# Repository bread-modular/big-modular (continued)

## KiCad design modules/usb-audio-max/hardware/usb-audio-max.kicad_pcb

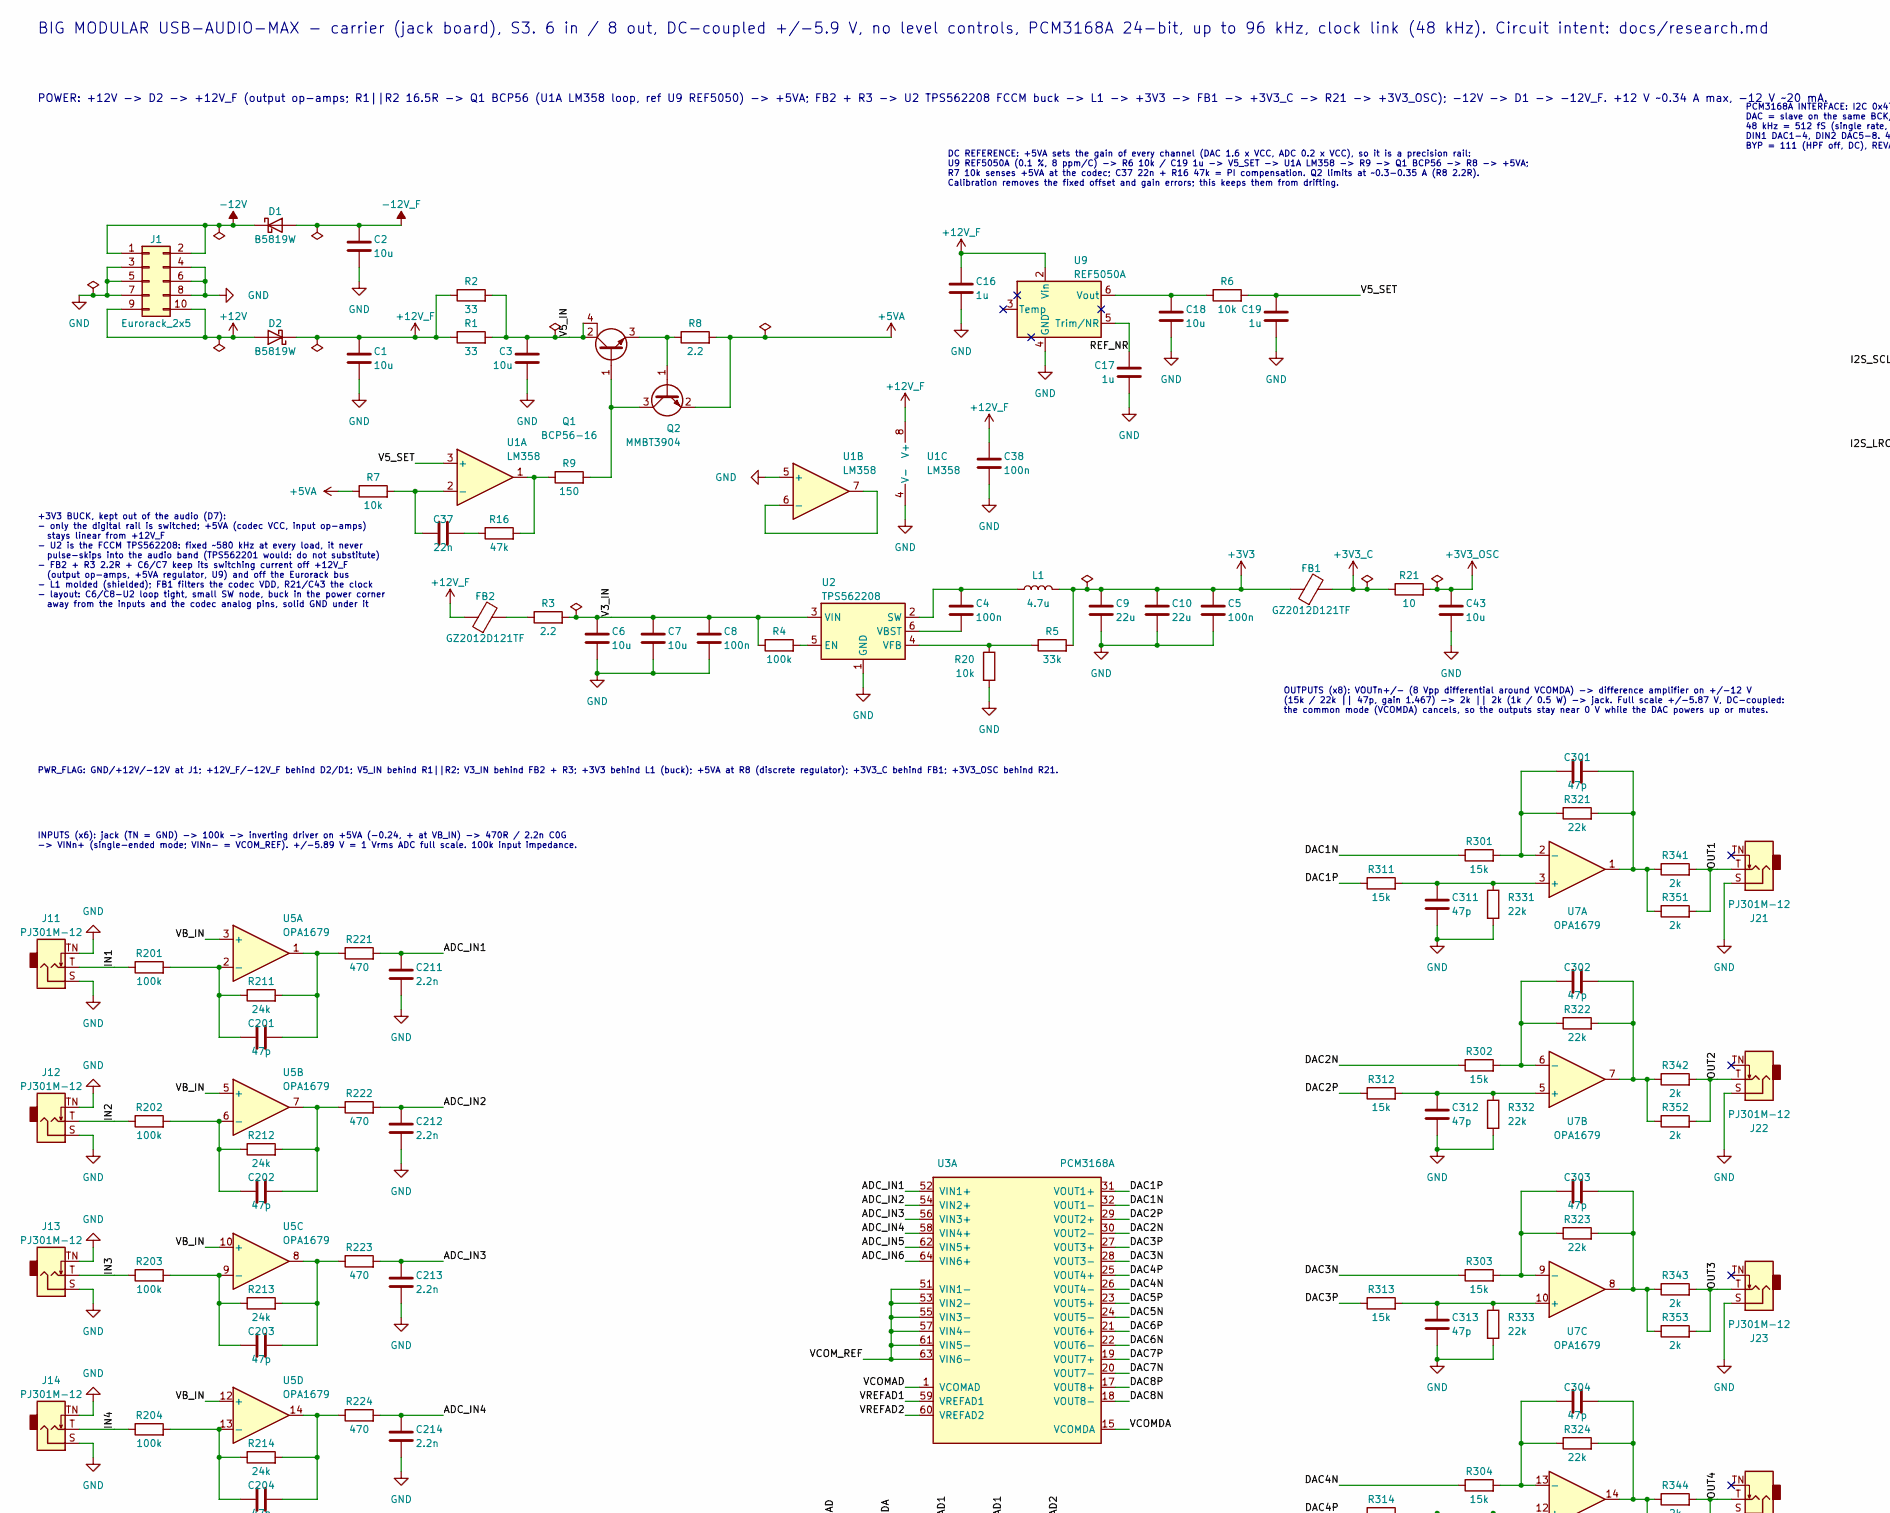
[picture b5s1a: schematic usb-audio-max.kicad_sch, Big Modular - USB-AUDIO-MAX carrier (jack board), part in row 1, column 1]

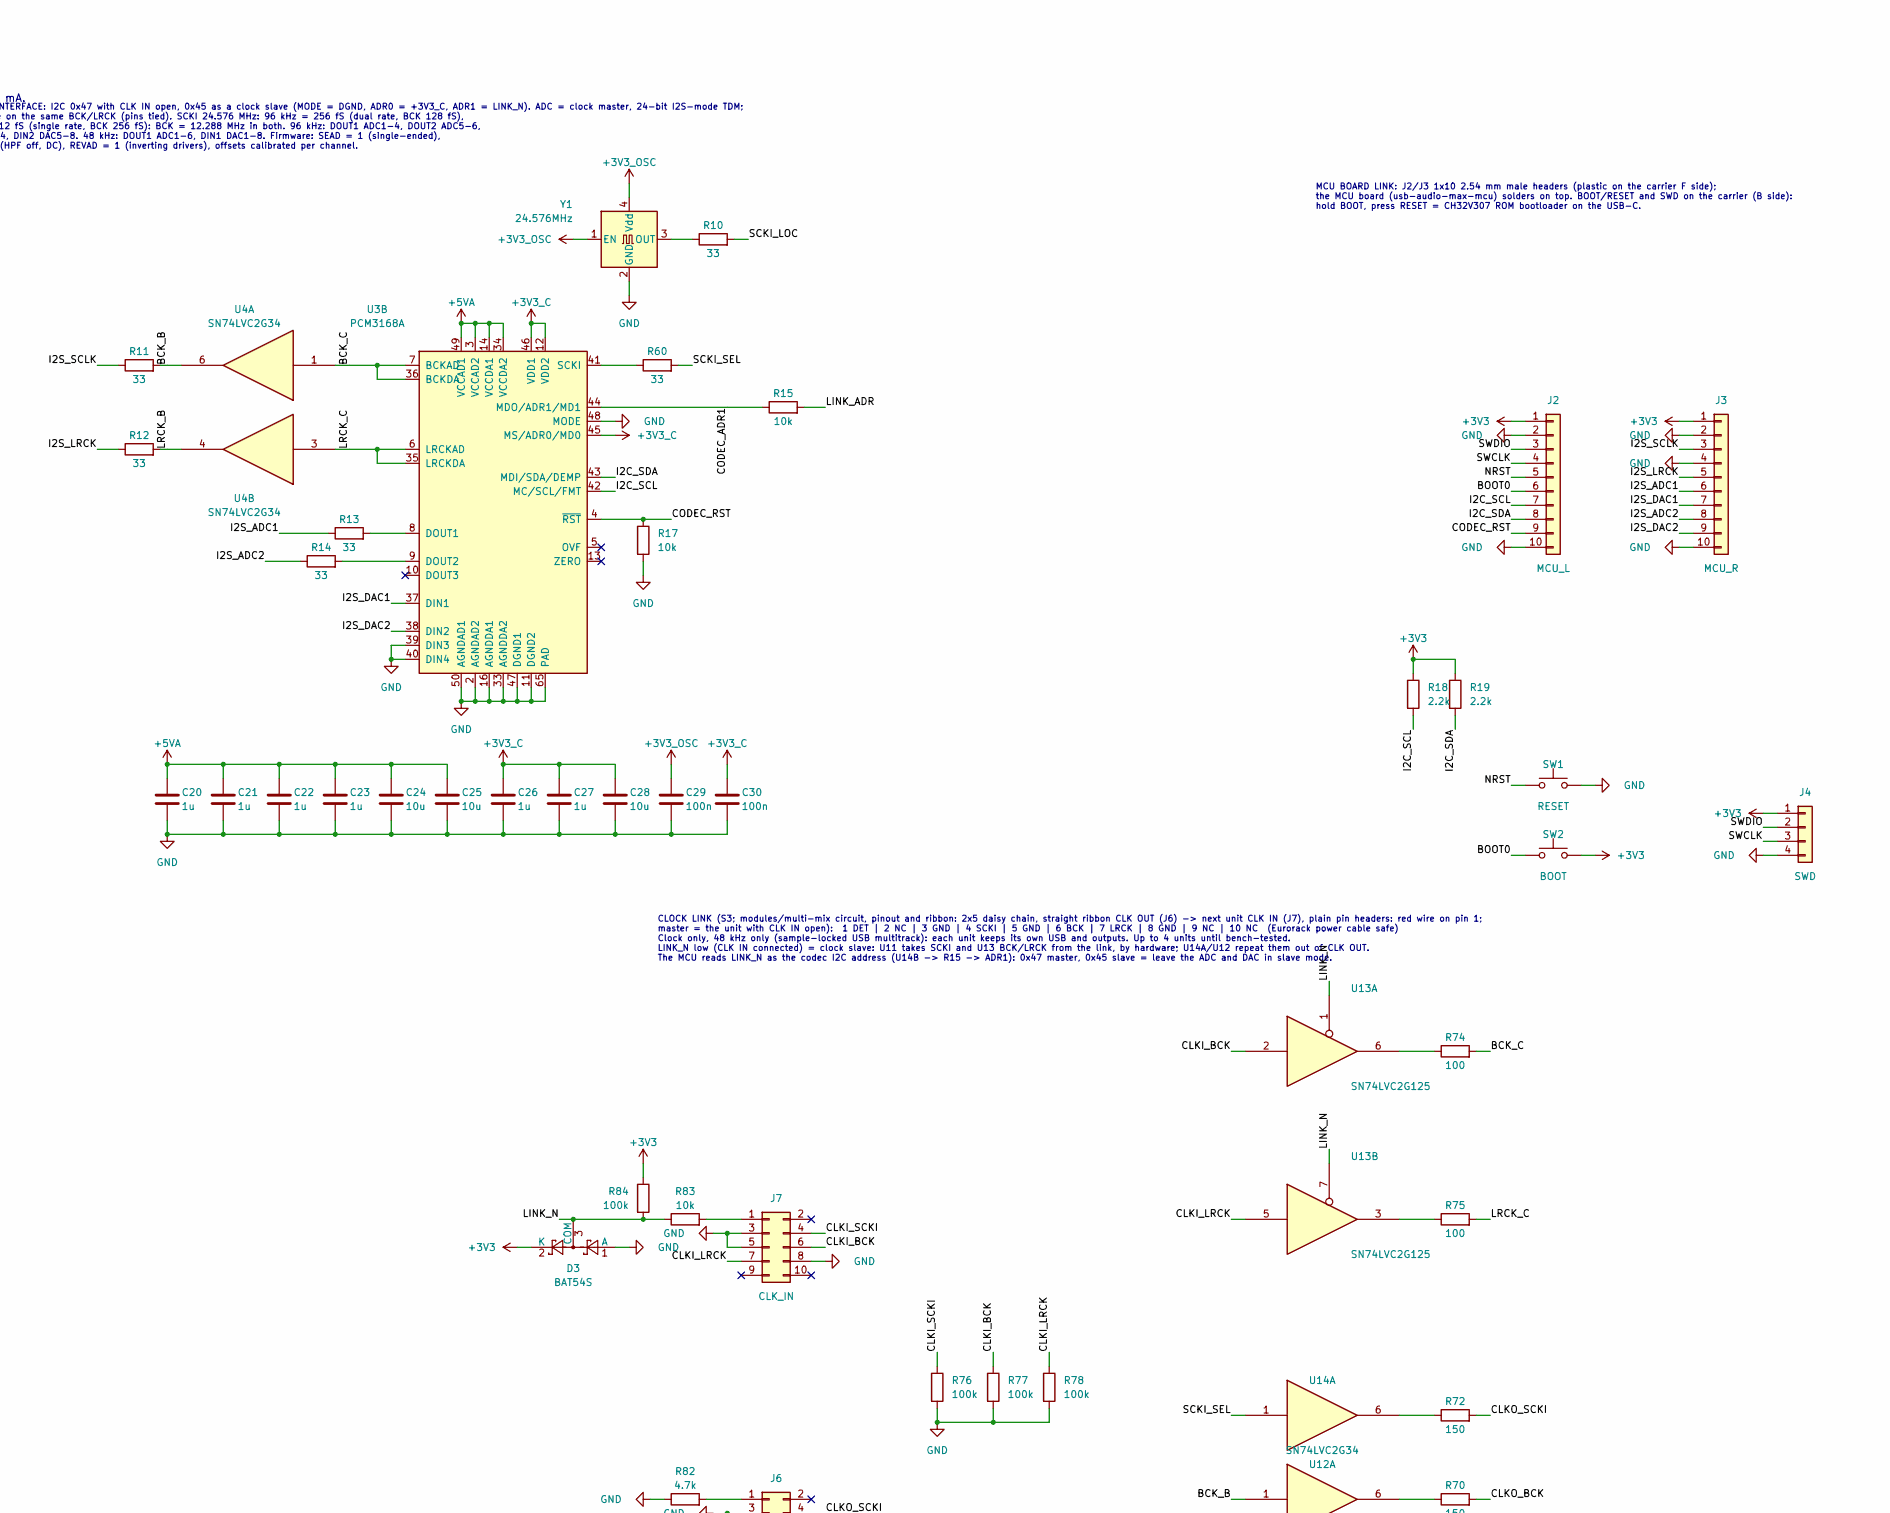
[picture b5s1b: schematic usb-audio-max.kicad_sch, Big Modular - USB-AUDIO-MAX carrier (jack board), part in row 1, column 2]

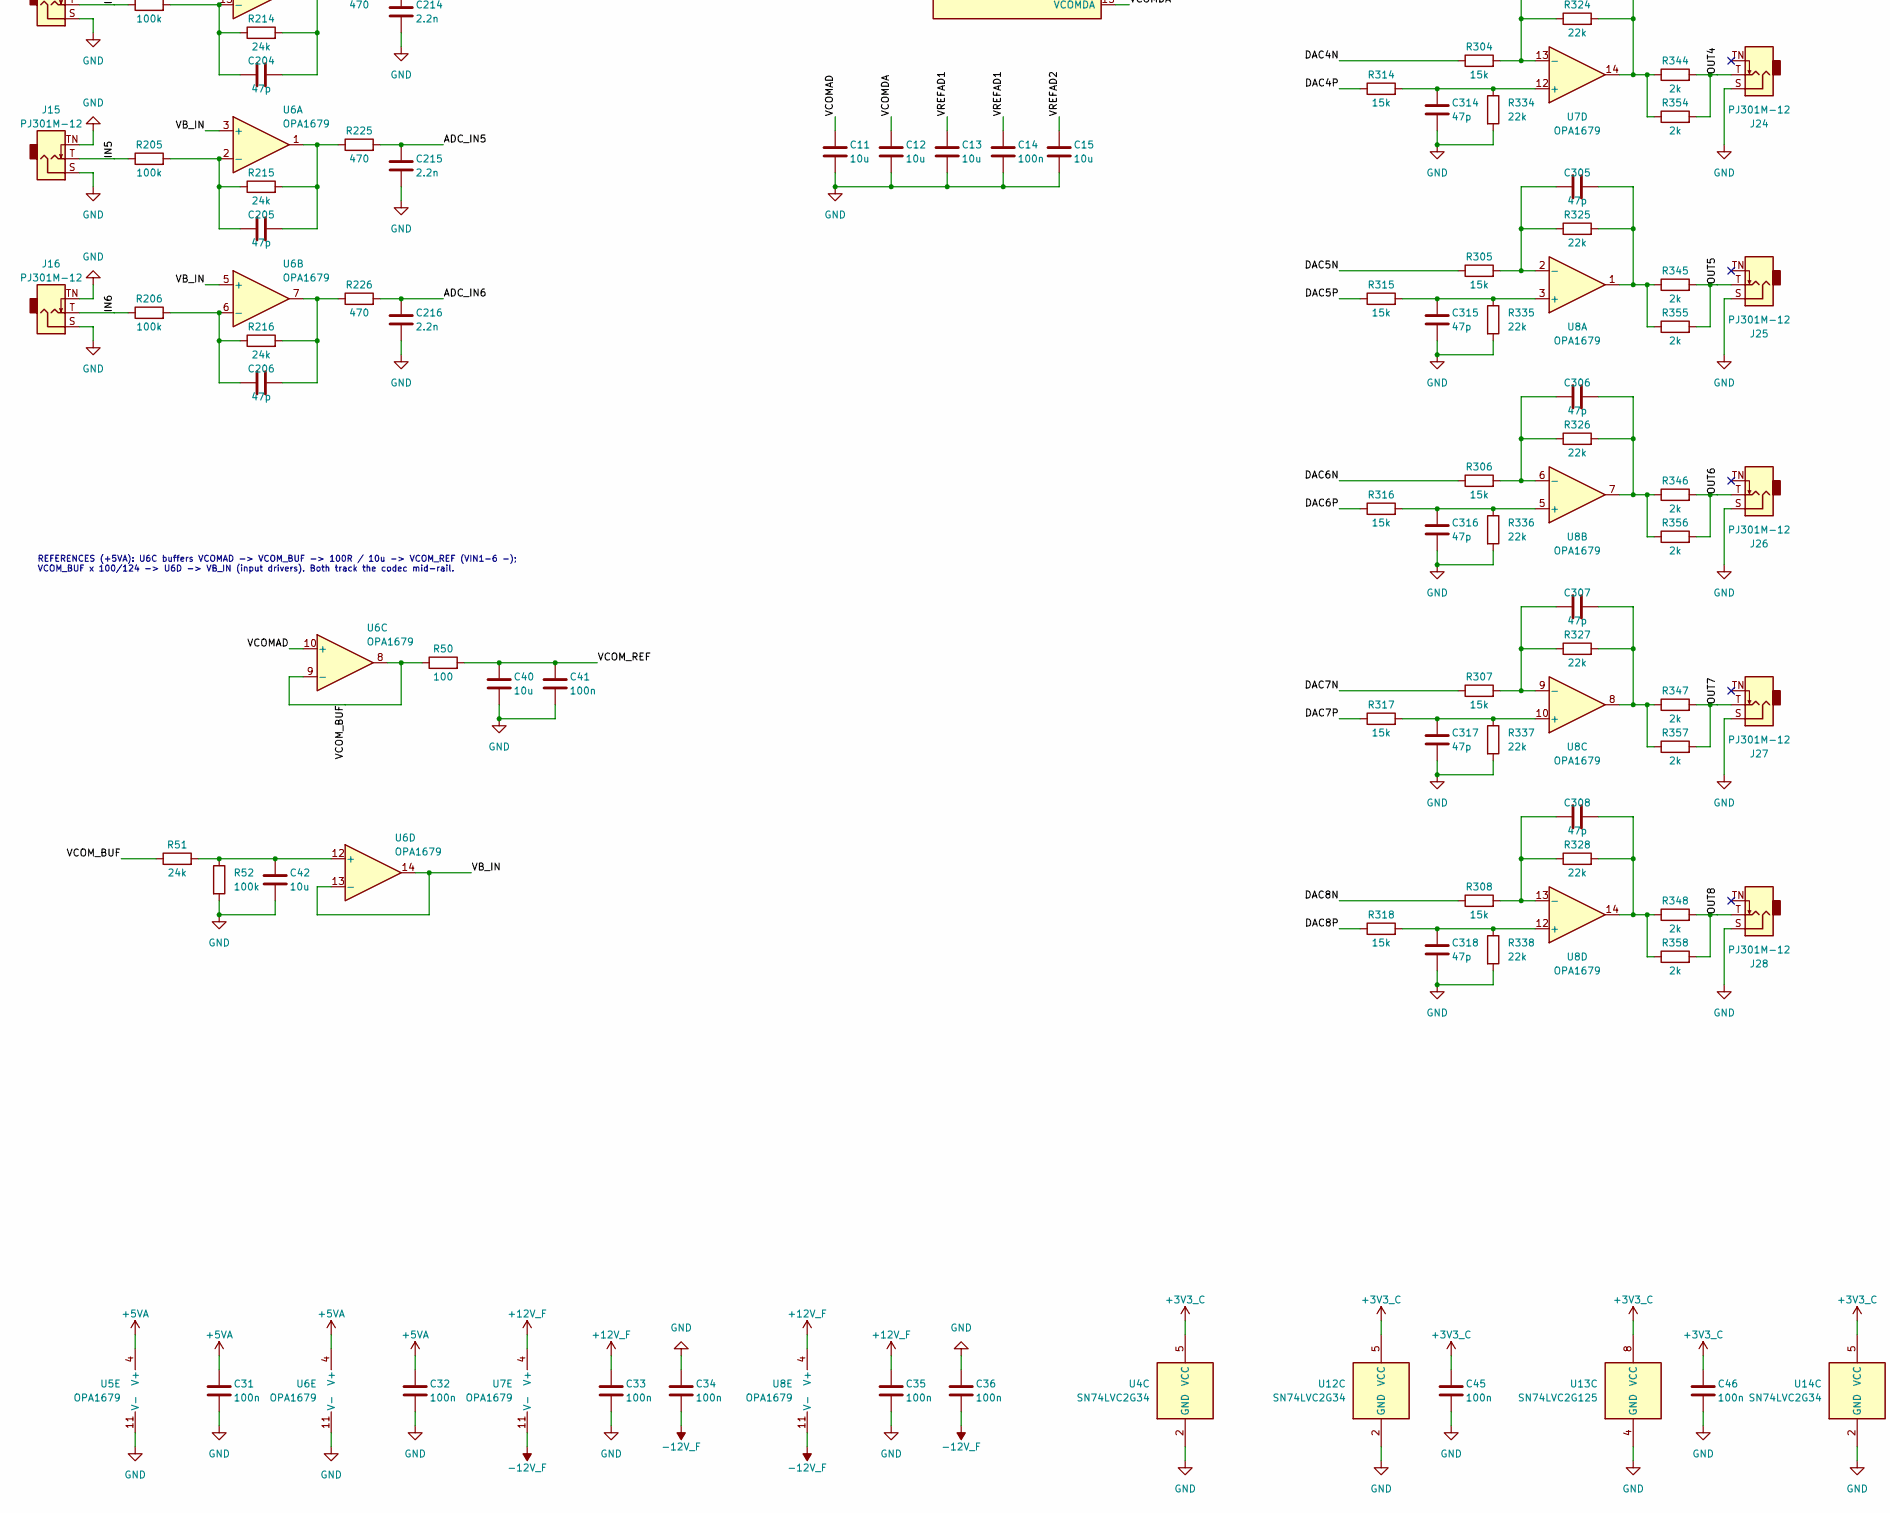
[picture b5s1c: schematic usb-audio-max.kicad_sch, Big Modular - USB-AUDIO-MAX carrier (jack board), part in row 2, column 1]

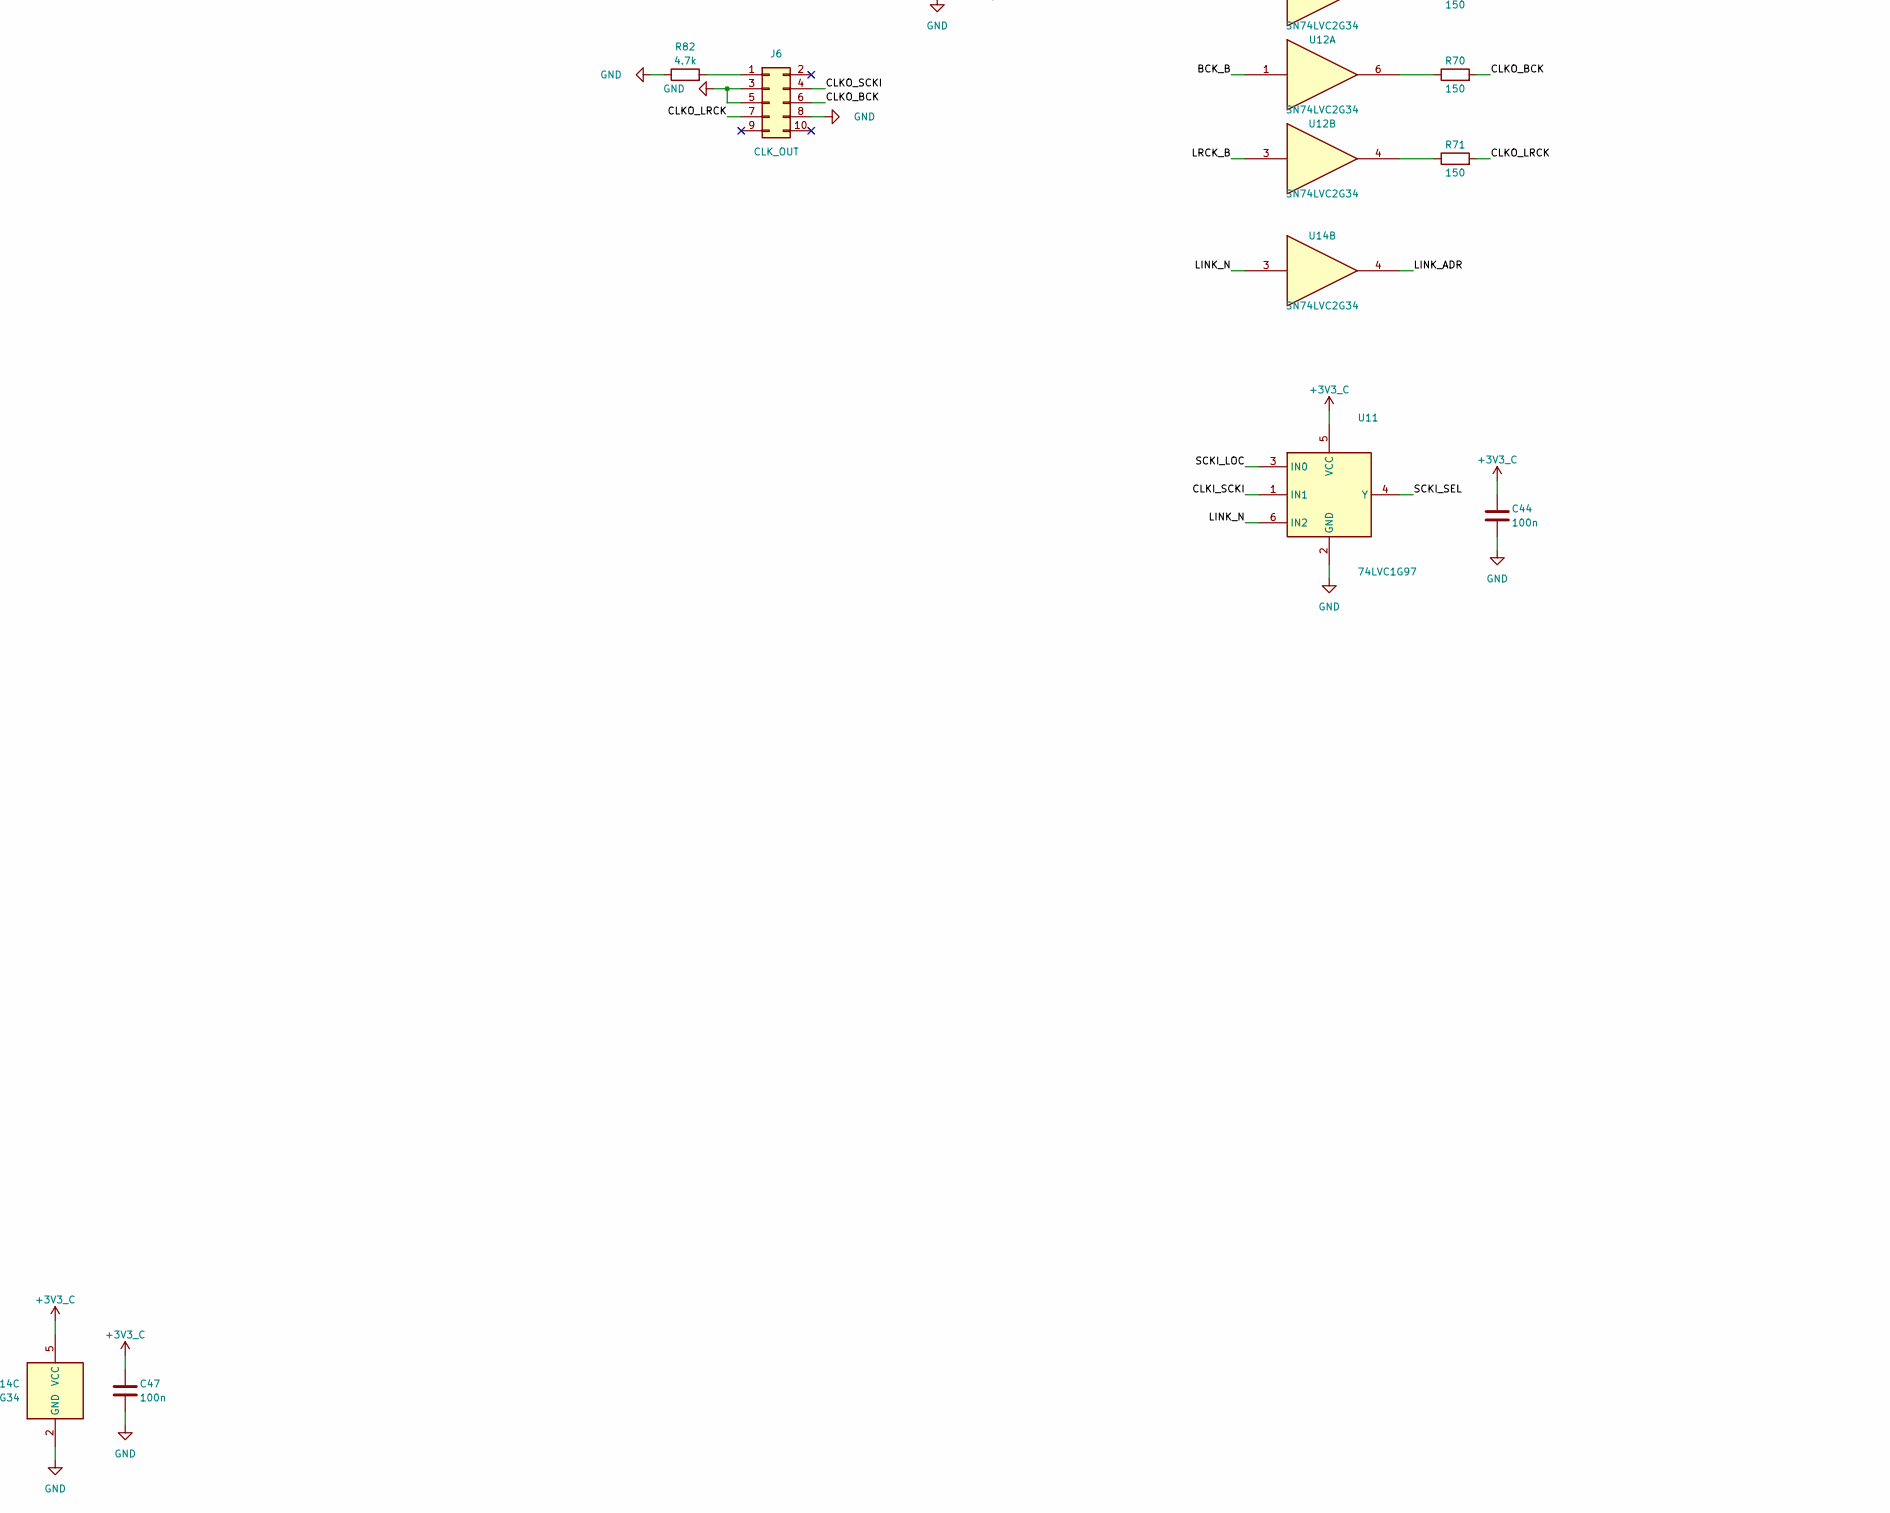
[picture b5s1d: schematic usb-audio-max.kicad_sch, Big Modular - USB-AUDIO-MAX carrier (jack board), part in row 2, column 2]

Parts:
C1, C2, C3, C11, C12, C13, C15, C18, C24, C25, C28, C40, C42, C43: 10u; C_0805_2012Metric; Voltage 25V; MPN CL21A106KAYNNNE; LCSC C15850
C4, C5, C8, C14, C29, C30, C31, C32, C33, C34, C35, C36, C38, C41, C44, C45, C46, C47: 100n; C_0603_1608Metric; Voltage 50V; MPN CC0603KRX7R9BB104; LCSC C14663
C6, C7: 10u; C_1206_3216Metric; Voltage 50V; MPN CL31A106KBHNNNE; LCSC C13585
C9, C10: 22u; C_0805_2012Metric; Voltage 25V; MPN CL21A226MAQNNNE; LCSC C45783
C16, C17, C19, C20, C21, C22, C23, C26, C27: 1u; C_0603_1608Metric; Voltage 50V; MPN CL10A105KB8NNNC; LCSC C15849
C37: 22n; C_0603_1608Metric; Voltage 50V; MPN CL10B223KB8NNNC; LCSC C21122
C201, C202, C203, C204, C205, C206, C301, C302, C303, C304, C305, C306, C307, C308, C311, C312, C313, C314, C315, C316, C317, C318: 47p; C_0603_1608Metric; Voltage 50V; MPN CL10C470JB8NNNC; LCSC C1671
C211, C212, C213, C214, C215, C216: 2.2n; C_0603_1608Metric; Voltage 50V; MPN CC0603JRNPO9BN222; LCSC C107043
D1, D2: B5819W; D_SOD-123; MPN B5819W SL; LCSC C8598
D3: BAT54S; SOT-23; MPN BAT54S,215; LCSC C47546
FB1, FB2: GZ2012D121TF; C_0805_2012Metric; MPN GZ2012D121TF; LCSC C5671
J1: Eurorack_2x5; PinHeader_2x05_P2.54mm_Vertical
J2: MCU_L; PinHeader_1x10_P2.54mm_Vertical; MPN 2.54 mm 1x10 male pin header (2.5 mm pl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
J3: MCU_R; PinHeader_1x10_P2.54mm_Vertical; MPN 2.54 mm 1x10 male pin header (2.5 mm pl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
J4: SWD; PinHeader_1x04_P2.54mm_Vertical
J6: CLK_OUT; PinHeader_2x05_P2.54mm_Vertical
J7: CLK_IN; PinHeader_2x05_P2.54mm_Vertical
J11, J12, J13, J14, J15, J16, J21, J22, J23, J24, J25, J26, J27, J28: PJ301M-12; Jack_3.5mm_QingPu_WQP-PJ301M-12_Vertical
L1: 4.7u; L_Sunlord_MWSA0402S; MPN MWSA0402S-4R7MT; LCSC C408337
Q1: BCP56-16; SOT-223; MPN BCP56-16,115; LCSC C92221
Q2: MMBT3904; SOT-23; MPN MMBT3904; LCSC C20526
R1, R2: 33; R_2512_6332Metric; MPN 25121WF330JT4E; LCSC C53728
R3, R8: 2.2; R_1206_3216Metric; Tolerance 1%; MPN AC1206FR-072R2L; LCSC C144499
R4, R52, R76, R77, R78, R84, R201, R202, R203, R204, R205, R206: 100k; R_0603_1608Metric; MPN 0603WAF1003T5E; LCSC C25803
R5: 33k; R_0603_1608Metric; MPN 0603WAF3302T5E; LCSC C4216
R6, R7, R15, R17, R20, R83: 10k; R_0603_1608Metric; MPN 0603WAF1002T5E; LCSC C25804
R9, R70, R71, R72: 150; R_0603_1608Metric; MPN 0603WAF1500T5E; LCSC C22808
R10, R11, R12, R13, R14, R60: 33; R_0603_1608Metric; MPN 0603WAF330JT5E; LCSC C23140
R16: 47k; R_0603_1608Metric; MPN 0603WAF4702T5E; LCSC C25819
R18, R19: 2.2k; R_0603_1608Metric; MPN 0603WAF2201T5E; LCSC C4190
R21: 10; R_0603_1608Metric; MPN 0603WAF100JT5E; LCSC C22859
R50, R74, R75: 100; R_0603_1608Metric; MPN 0603WAF1000T5E; LCSC C22775
R51, R211, R212, R213, R214, R215, R216: 24k; R_0603_1608Metric; MPN 0603WAF2402T5E; LCSC C23352
R82: 4.7k; R_0603_1608Metric; MPN 0603WAF4701T5E; LCSC C23162
R221, R222, R223, R224, R225, R226: 470; R_0603_1608Metric; MPN 0603WAF4700T5E; LCSC C23179
R301, R302, R303, R304, R305, R306, R307, R308, R311, R312, R313, R314, R315, R316, R317, R318: 15k; R_0603_1608Metric; Tolerance 1%; MPN 0603WAF1502T5E; LCSC C22809
R321, R322, R323, R324, R325, R326, R327, R328, R331, R332, R333, R334, R335, R336, R337, R338: 22k; R_0603_1608Metric; Tolerance 1%; MPN 0603WAF2202T5E; LCSC C31850
R341, R342, R343, R344, R345, R346, R347, R348, R351, R352, R353, R354, R355, R356, R357, R358: 2k; R_1206_3216Metric; Tolerance 1%; MPN 1206W4F2001T5E; LCSC C17944
SW1: RESET; K2-1808SN-A4SW-01; MPN K2-1808SN-A4SW-01; LCSC C92589
SW2: BOOT; K2-1808SN-A4SW-01; MPN K2-1808SN-A4SW-01; LCSC C92589
U1: LM358; SOIC-8_3.9x4.9mm_P1.27mm; MPN LM358DR2G; LCSC C7950
U2: TPS562208; SOT-23-6; MPN TPS562208DDCR; LCSC C91301
U3: PCM3168A; PCM3168A_HTQFP-64-1EP_10x10mm_P0.5mm_EP8x8mm_Mask7.4x7.4mm_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; MPN PCM3168APAPR; LCSC C529289
U4, U12, U14: SN74LVC2G34; SOT-363_SC-70-6; MPN SN74LVC2G34DCKR; LCSC C14461
U5, U6, U7, U8: OPA1679; SOIC-14_3.9x8.7mm_P1.27mm; MPN OPA1679IDR; LCSC C2878631
U9: REF5050A; SOIC-8_3.9x4.9mm_P1.27mm; MPN REF5050AIDR; LCSC C27804
U11: 74LVC1G97; SOT-363_SC-70-6; MPN 74LVC1G97DW-7; LCSC C460532
U13: SN74LVC2G125; SSOP-8_2.95x2.8mm_P0.65mm; MPN SN74LVC2G125DCTR; LCSC C206035
Y1: 24.576MHz; Oscillator_SMD_Abracon_ASE-4Pin_3.2x2.5mm; MPN OT2EL4C4JI-111OLP-24.576M; LCSC C5203547

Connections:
+3V3: C5.1, C9.1, C10.1, D3.2 (K), FB1.1, J2.1, J3.1, J4.1, L1.2, R5.2, R18.1, R19.1, R84.1, SW2.2
+3V3_C: C26.1, C27.1, C28.1, C30.1, C44.1, C45.1, C46.1, C47.1, FB1.2, R21.1, U3.12 (VDD2), U3.45 (MS/ADR0/MD0), U3.46 (VDD1), U4.5 (VCC), U11.5 (VCC), U12.5 (VCC), U13.8 (VCC), U14.5 (VCC)
+3V3_OSC: C29.1, C43.1, R21.2, Y1.1 (EN), Y1.4 (Vdd)
+5VA: C20.1, C21.1, C22.1, C23.1, C24.1, C25.1, C31.1, C32.1, Q2.2 (E), R7.1, R8.2, U3.3 (VCCAD2), U3.14 (VCCDA1), U3.34 (VCCDA2), U3.49 (VCCAD1), U5.4 (V+), U6.4 (V+)
+12V: D2.2 (A), J1.9, J1.10
+12V_F: C1.1, C16.1, C33.1, C35.1, C38.1, D2.1 (K), FB2.1, R1.1, R2.1, U1.8 (V+), U7.4 (V+), U8.4 (V+), U9.2 (Vin)
-12V: D1.1 (K), J1.1, J1.2
-12V_F: C2.2, C34.2, C36.2, D1.2 (A), U7.11 (V-), U8.11 (V-)
/ADC_IN1: C211.1, R221.2, U3.52 (VIN1+)
/ADC_IN2: C212.1, R222.2, U3.54 (VIN2+)
/ADC_IN3: C213.1, R223.2, U3.56 (VIN3+)
/ADC_IN4: C214.1, R224.2, U3.58 (VIN4+)
/ADC_IN5: C215.1, R225.2, U3.62 (VIN5+)
/ADC_IN6: C216.1, R226.2, U3.64 (VIN6+)
/BCK_B: R11.2, U4.6, U12.1
/BCK_C: R74.2, U3.7 (BCKAD), U3.36 (BCKDA), U4.1
/BOOT0: J2.6, SW2.1
/CLKI_BCK: J7.6, R77.1, U13.2
/CLKI_LRCK: J7.7, R78.1, U13.5
/CLKI_SCKI: J7.4, R76.1, U11.1 (IN1)
/CLKO_BCK: J6.6, R70.2
/CLKO_LRCK: J6.7, R71.2
/CLKO_SCKI: J6.4, R72.2
/CODEC_ADR1: R15.1, U3.44 (MDO/ADR1/MD1)
/CODEC_RST: J2.9, R17.1, U3.4 (~RST)
/DAC1N: R301.1, U3.32 (VOUT1-)
/DAC1P: R311.1, U3.31 (VOUT1+)
/DAC2N: R302.1, U3.30 (VOUT2-)
/DAC2P: R312.1, U3.29 (VOUT2+)
/DAC3N: R303.1, U3.28 (VOUT3-)
/DAC3P: R313.1, U3.27 (VOUT3+)
/DAC4N: R304.1, U3.26 (VOUT4-)
/DAC4P: R314.1, U3.25 (VOUT4+)
/DAC5N: R305.1, U3.24 (VOUT5-)
/DAC5P: R315.1, U3.23 (VOUT5+)
/DAC6N: R306.1, U3.22 (VOUT6-)
/DAC6P: R316.1, U3.21 (VOUT6+)
/DAC7N: R307.1, U3.20 (VOUT7-)
/DAC7P: R317.1, U3.19 (VOUT7+)
/DAC8N: R308.1, U3.18 (VOUT8-)
/DAC8P: R318.1, U3.17 (VOUT8+)
/I2C_SCL: J2.7, R18.2, U3.42 (MC/SCL/FMT)
/I2C_SDA: J2.8, R19.2, U3.43 (MDI/SDA/DEMP)
/I2S_ADC1: J3.6, R13.1
/I2S_ADC2: J3.8, R14.1
/I2S_DAC1: J3.7, U3.37 (DIN1)
/I2S_DAC2: J3.9, U3.38 (DIN2)
/I2S_LRCK: J3.5, R12.1
/I2S_SCLK: J3.3, R11.1
/IN1: J11.T, R201.1
/IN2: J12.T, R202.1
/IN3: J13.T, R203.1
/IN4: J14.T, R204.1
/IN5: J15.T, R205.1
/IN6: J16.T, R206.1
/LINK_ADR: R15.2, U14.4
/LINK_N: D3.3 (COM), R83.1, R84.2, U11.6 (IN2), U13.1, U13.7, U14.3
/LRCK_B: R12.2, U4.4, U12.3
/LRCK_C: R75.2, U3.6 (LRCKAD), U3.35 (LRCKDA), U4.3
/NRST: J2.5, SW1.1
/OUT1: J21.T, R341.2, R351.2
/OUT2: J22.T, R342.2, R352.2
/OUT3: J23.T, R343.2, R353.2
/OUT4: J24.T, R344.2, R354.2
/OUT5: J25.T, R345.2, R355.2
/OUT6: J26.T, R346.2, R356.2
/OUT7: J27.T, R347.2, R357.2
/OUT8: J28.T, R348.2, R358.2
/REF_NR: C17.1, U9.5 (Trim/NR)
/SCKI_LOC: R10.2, U11.3 (IN0)
/SCKI_SEL: R60.2, U11.4 (Y), U14.1
/SWCLK: J2.4, J4.3
/SWDIO: J2.3, J4.2
/V3_IN: C6.1, C7.1, C8.1, R3.2, R4.1, U2.3 (VIN)
/V5_IN: C3.1, Q1.2 (C), Q1.4 (C), R1.2, R2.2
/V5_SET: C19.1, R6.2, U1.3 (+)
/VB_IN: U5.3 (+), U5.5 (+), U5.10 (+), U5.12 (+), U6.3 (+), U6.5 (+), U6.13 (-), U6.14
/VCOMAD: C11.1, U3.1 (VCOMAD), U6.10 (+)
/VCOMDA: C12.1, U3.15 (VCOMDA)
/VCOM_BUF: R50.1, R51.1, U6.8, U6.9 (-)
/VCOM_REF: C40.1, C41.1, R50.2, U3.51 (VIN1-), U3.53 (VIN2-), U3.55 (VIN3-), U3.57 (VIN4-), U3.61 (VIN5-), U3.63 (VIN6-)
/VREFAD1: C13.1, C14.1, U3.59 (VREFAD1)
/VREFAD2: C15.1, U3.60 (VREFAD2)
GND: C1.2, C2.1, C3.2, C5.2, C6.2, C7.2, C8.2, C9.2, C10.2, C11.2, C12.2, C13.2, C14.2, C15.2, C16.2, C17.2, C18.2, C19.2, C20.2, C21.2, C22.2, C23.2, C24.2, C25.2, C26.2, C27.2, C28.2, C29.2, C30.2, C31.2, C32.2, C33.2, C34.1, C35.2, C36.1, C38.2, C40.2, C41.2, C42.2, C43.2, C44.2, C45.2, C46.2, C47.2, C211.2, C212.2, C213.2, C214.2, C215.2, C216.2, C311.2, C312.2, C313.2, C314.2, C315.2, C316.2, C317.2, C318.2, D3.1 (A), J1.3, J1.4, J1.5, J1.6, J1.7, J1.8, J2.2, J2.10, J3.2, J3.4, J3.10, J4.4, J6.3, J6.5, J6.8, J7.3, J7.5, J7.8, J11.S, J11.TN, J12.S, J12.TN, J13.S, J13.TN, J14.S, J14.TN, J15.S, J15.TN, J16.S, J16.TN, J21.S, J22.S, J23.S, J24.S, J25.S, J26.S, J27.S, J28.S, R17.2, R20.2, R52.2, R76.2, R77.2, R78.2, R82.1, R331.2, R332.2, R333.2, R334.2, R335.2, R336.2, R337.2, R338.2, SW1.2, U1.4 (V-), U1.5 (+), U2.1 (GND), U3.2 (AGNDAD2), U3.11 (DGND2), U3.16 (AGNDDA1), U3.33 (AGNDDA2), U3.39 (DIN3), U3.40 (DIN4), U3.47 (DGND1), U3.48 (MODE), U3.50 (AGNDAD1), U3.65 (PAD), U4.2 (GND), U5.11 (V-), U6.11 (V-), U9.4 (GND), U11.2 (GND), U12.2 (GND), U13.4 (GND), U14.2 (GND), Y1.2 (GND)
unnamed: C37.2, R16.1
unnamed: C201.2, R211.2, R221.1, U5.1
unnamed: C202.2, R212.2, R222.1, U5.7
unnamed: C203.2, R213.2, R223.1, U5.8
unnamed: C204.2, R214.2, R224.1, U5.14
unnamed: C205.2, R215.2, R225.1, U6.1
unnamed: C206.2, R216.2, R226.1, U6.7
unnamed: C301.2, R321.2, R341.1, R351.1, U7.1
unnamed: C302.2, R322.2, R342.1, R352.1, U7.7
unnamed: C303.2, R323.2, R343.1, R353.1, U7.8
unnamed: C304.2, R324.2, R344.1, R354.1, U7.14
unnamed: C305.2, R325.2, R345.1, R355.1, U8.1
unnamed: C306.2, R326.2, R346.1, R356.1, U8.7
unnamed: C307.2, R327.2, R347.1, R357.1, U8.8
unnamed: C308.2, R328.2, R348.1, R358.1, U8.14
unnamed: FB2.2, R3.1
unnamed: J6.1, R82.2
unnamed: J7.1, R83.2
unnamed: Q1.1 (B), Q2.3 (C), R9.2
unnamed: Q1.3 (E), Q2.1 (B), R8.1
unnamed: R9.1, R16.2, U1.1
unnamed: R70.1, U12.6
unnamed: R71.1, U12.4
unnamed: R72.1, U14.6
unnamed: R74.1, U13.6
unnamed: R75.1, U13.3
unnamed: C37.1, R7.2, U1.2 (-)
unnamed: U1.6 (-), U1.7
unnamed: R4.2, U2.5 (EN)
unnamed: C4.1, L1.1, U2.2 (SW)
unnamed: C4.2, U2.6 (VBST)
unnamed: R5.1, R20.1, U2.4 (VFB)
unnamed: R13.2, U3.8 (DOUT1)
unnamed: R14.2, U3.9 (DOUT2)
unnamed: R60.1, U3.41 (SCKI)
unnamed: C201.1, R201.2, R211.1, U5.2 (-)
unnamed: C202.1, R202.2, R212.1, U5.6 (-)
unnamed: C203.1, R203.2, R213.1, U5.9 (-)
unnamed: C204.1, R204.2, R214.1, U5.13 (-)
unnamed: C205.1, R205.2, R215.1, U6.2 (-)
unnamed: C206.1, R206.2, R216.1, U6.6 (-)
unnamed: C42.1, R51.2, R52.1, U6.12 (+)
unnamed: C311.1, R311.2, R331.1, U7.3 (+)
unnamed: C301.1, R301.2, R321.1, U7.2 (-)
unnamed: C312.1, R312.2, R332.1, U7.5 (+)
unnamed: C302.1, R302.2, R322.1, U7.6 (-)
unnamed: C313.1, R313.2, R333.1, U7.10 (+)
unnamed: C303.1, R303.2, R323.1, U7.9 (-)
unnamed: C314.1, R314.2, R334.1, U7.12 (+)
unnamed: C304.1, R304.2, R324.1, U7.13 (-)
unnamed: C315.1, R315.2, R335.1, U8.3 (+)
unnamed: C305.1, R305.2, R325.1, U8.2 (-)
unnamed: C316.1, R316.2, R336.1, U8.5 (+)
unnamed: C306.1, R306.2, R326.1, U8.6 (-)
unnamed: C317.1, R317.2, R337.1, U8.10 (+)
unnamed: C307.1, R307.2, R327.1, U8.9 (-)
unnamed: C318.1, R318.2, R338.1, U8.12 (+)
unnamed: C308.1, R308.2, R328.1, U8.13 (-)
unnamed: C18.1, R6.1, U9.6 (Vout)
unnamed: R10.1, Y1.3 (OUT)

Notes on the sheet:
POWER: +12V -> D2 -> +12V_F (output op-amps; R1||R2 16.5R -> Q1 BCP56 (U1A LM358 loop, ref U9 REF5050) -> +5VA; FB2 + R3 -> U2 TPS562208 FCCM buck -> L1 -> +3V3 -> FB1 -> +3V3_C -> R21 -> +3V3_OSC); -12V -> D1 -> -12V_F. +12 V ~0.34 A max, -12 V ~20 mA.
+3V3 BUCK, kept out of the audio (D7): - only the digital rail is switched; +5VA (codec VCC, input op-amps) stays linear from +12V_F - U2 is the FCCM TPS562208: fixed ~580 kHz at every load, it never pulse-skips into the audio band (TPS562201 would: do not substitute) - FB2 + R3 2.2R + C6/C7 keep i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
BIG MODULAR USB-AUDIO-MAX - carrier (jack board), S3. 6 in / 8 out, DC-coupled +/-5.9 V, no level controls, PCM3168A 24-bit, up to 96 kHz, clock link (48 kHz). Circuit intent: docs/research.md
CLOCK LINK (S3; modules/multi-mix circuit, pinout and ribbon: 2x5 daisy chain, straight ribbon CLK OUT (J6) -> next unit CLK IN (J7), plain pin headers: red wire on pin 1; master = the unit with CLK IN open): 1 DET | 2 NC | 3 GND | 4 SCKI | 5 GND | 6 BCK | 7 LRCK | 8 GND | 9 NC | 10 NC (Eurorack po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
OUTPUTS (x8): VOUTn+/- (8 Vpp differential around VCOMDA) -> difference amplifier on +/-12 V (15k / 22k || 47p, gain 1.467) -> 2k || 2k (1k / 0.5 W) -> jack. Full scale +/-5.87 V, DC-coupled: the common mode (VCOMDA) cancels, so the outputs stay near 0 V while the DAC powers up or mutes.
DC REFERENCE: +5VA sets the gain of every channel (DAC 1.6 x VCC, ADC 0.2 x VCC), so it is a precision rail: U9 REF5050A (0.1 %, 8 ppm/C) -> R6 10k / C19 1u -> V5_SET -> U1A LM358 -> R9 -> Q1 BCP56 -> R8 -> +5VA; R7 10k senses +5VA at the codec; C37 22n + R16 47k = PI compensation. Q2 limits at ~0.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
PCM3168A INTERFACE: I2C 0x47 with CLK IN open, 0x45 as a clock slave (MODE = DGND, ADR0 = +3V3_C, ADR1 = LINK_N). ADC = clock master, 24-bit I2S-mode TDM; DAC = slave on the same BCK/LRCK (pins tied). SCKI 24.576 MHz: 96 kHz = 256 fS (dual rate, BCK 128 fS), 48 kHz = 512 fS (single rate, BCK 256 fS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
REFERENCES (+5VA): U6C buffers VCOMAD -> VCOM_BUF -> 100R / 10u -> VCOM_REF (VIN1-6 -); VCOM_BUF x 100/124 -> U6D -> VB_IN (input drivers). Both track the codec mid-rail.
PWR_FLAG: GND/+12V/-12V at J1; +12V_F/-12V_F behind D2/D1; V5_IN behind R1||R2; V3_IN behind FB2 + R3; +3V3 behind L1 (buck); +5VA at R8 (discrete regulator); +3V3_C behind FB1; +3V3_OSC behind R21.
INPUTS (x6): jack (TN = GND) -> 100k -> inverting driver on +5VA (-0.24, + at VB_IN) -> 470R / 2.2n C0G -> VINn+ (single-ended mode; VINn- = VCOM_REF). +/-5.89 V = 1 Vrms ADC full scale. 100k input impedance.
MCU BOARD LINK: J2/J3 1x10 2.54 mm male headers (plastic on the carrier F side); the MCU board (usb-audio-max-mcu) solders on top. BOOT/RESET and SWD on the carrier (B side): hold BOOT, press RESET = CH32V307 ROM bootloader on the USB-C.

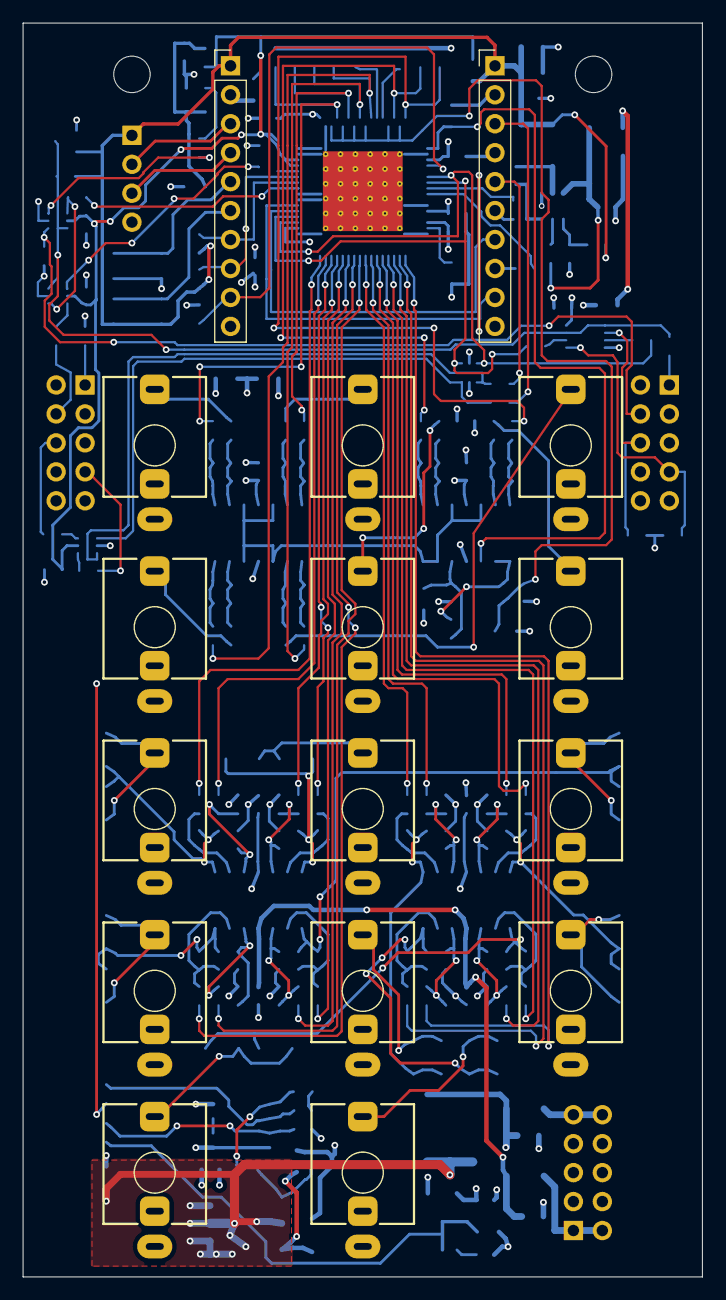
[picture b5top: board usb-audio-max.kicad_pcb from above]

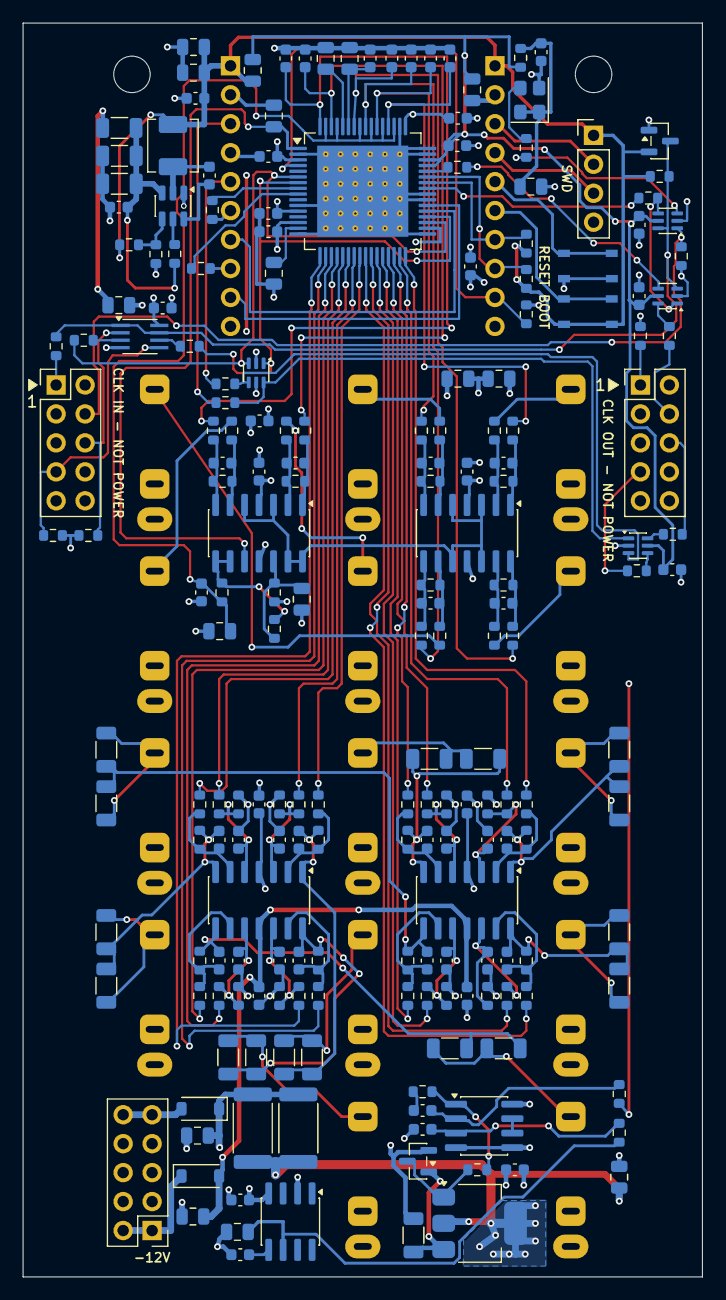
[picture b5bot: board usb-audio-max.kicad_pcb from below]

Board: 4 copper layers, 59.6 x 110.0 mm, 220 parts (204 on the bottom side), 144 nets.
